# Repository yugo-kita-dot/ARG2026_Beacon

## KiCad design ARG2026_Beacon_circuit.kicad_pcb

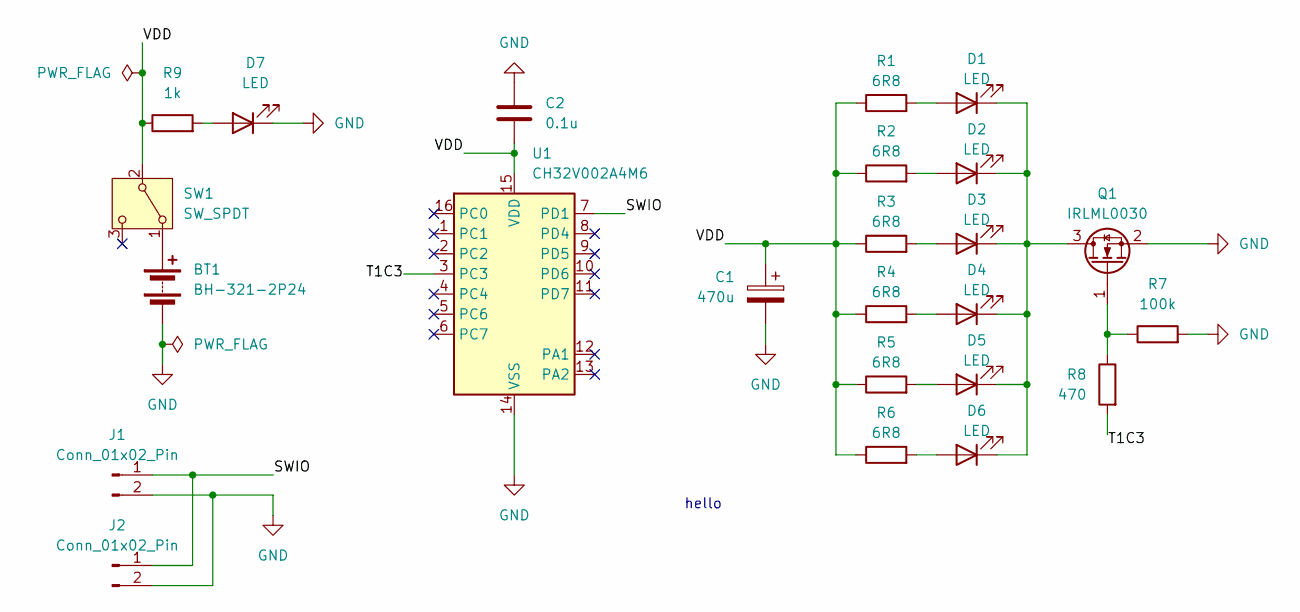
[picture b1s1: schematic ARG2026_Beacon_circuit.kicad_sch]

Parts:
BT1: BH-321-2P24
C1: 470u; CP_Radial_D8.0mm_P3.50mm
C2: 0.1u; C_Rect_L4.0mm_W2.5mm_P2.50mm
D1, D2, D3, D4, D5, D6: LED; LED_Rectangular_W5.0mm_H2.0mm
D7: LED; LED_D3.0mm
J1, J2: Conn_01x02_Pin; PinHeader_1x02_P2.54mm_Vertical
Q1: IRLML0030; SOT-23
R1, R2, R3, R4, R5, R6: 6R8; R_Axial_DIN0207_L6.3mm_D2.5mm_P10.16mm_Horizontal
R7: 100k; R_Axial_DIN0207_L6.3mm_D2.5mm_P10.16mm_Horizontal
R8: 470; R_Axial_DIN0207_L6.3mm_D2.5mm_P10.16mm_Horizontal
R9: 1k; R_Axial_DIN0207_L6.3mm_D2.5mm_P10.16mm_Horizontal
SW1: SW_SPDT; SW_Slide-03_Wuerth-WS-SLTV_10x2.5x6.4_P2.54mm
U1: CH32V002A4M6; STC_SOP-16_3.9x9.9mm_P1.27mm

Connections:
/SWIO: J1.1, J2.1, U1.7 (PD1)
/T1C3: R8.2, U1.3 (PC3)
/VDD: C1.1, C2.2, R1.1, R2.1, R3.1, R4.1, R5.1, R6.1, R9.1, SW1.2 (B), U1.15 (VDD)
GND: BT1.2 (-), C1.2, C2.1, D7.1 (K), J1.2, J2.2, Q1.2 (S), R7.2, U1.14 (VSS)
unnamed: BT1.1 (+), SW1.1 (A)
unnamed: D1.2 (A), R1.2
unnamed: D1.1 (K), D2.1 (K), D3.1 (K), D4.1 (K), D5.1 (K), D6.1 (K), Q1.3 (D)
unnamed: D2.2 (A), R2.2
unnamed: D3.2 (A), R3.2
unnamed: D4.2 (A), R4.2
unnamed: D5.2 (A), R5.2
unnamed: D6.2 (A), R6.2
unnamed: D7.2 (A), R9.2
unnamed: Q1.1 (G), R7.1, R8.1

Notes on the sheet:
hello

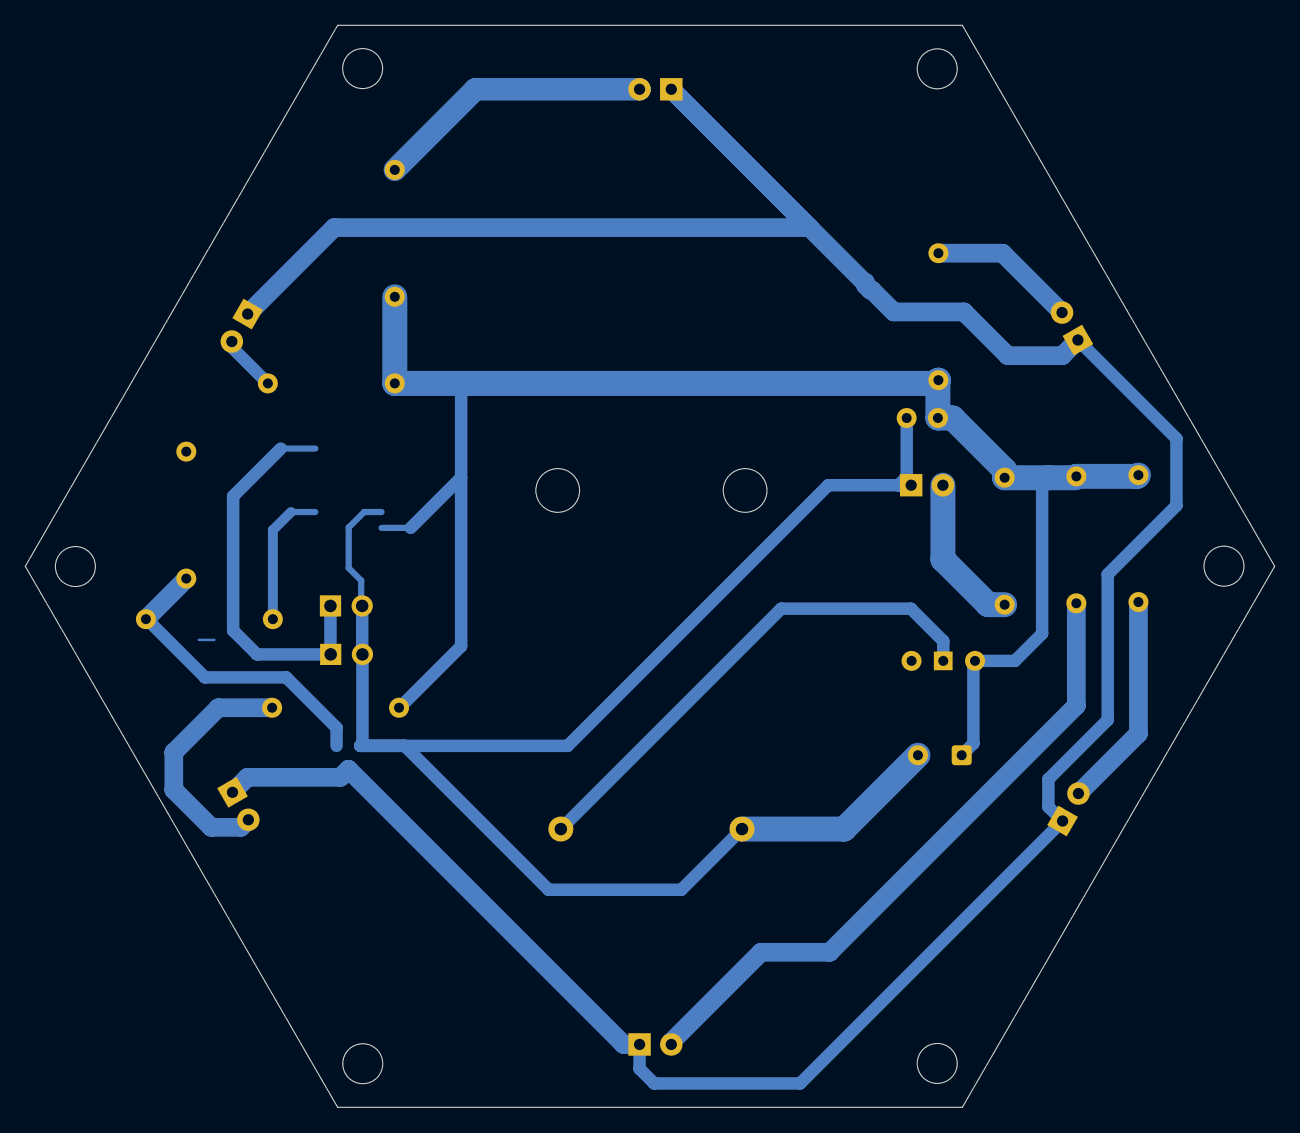
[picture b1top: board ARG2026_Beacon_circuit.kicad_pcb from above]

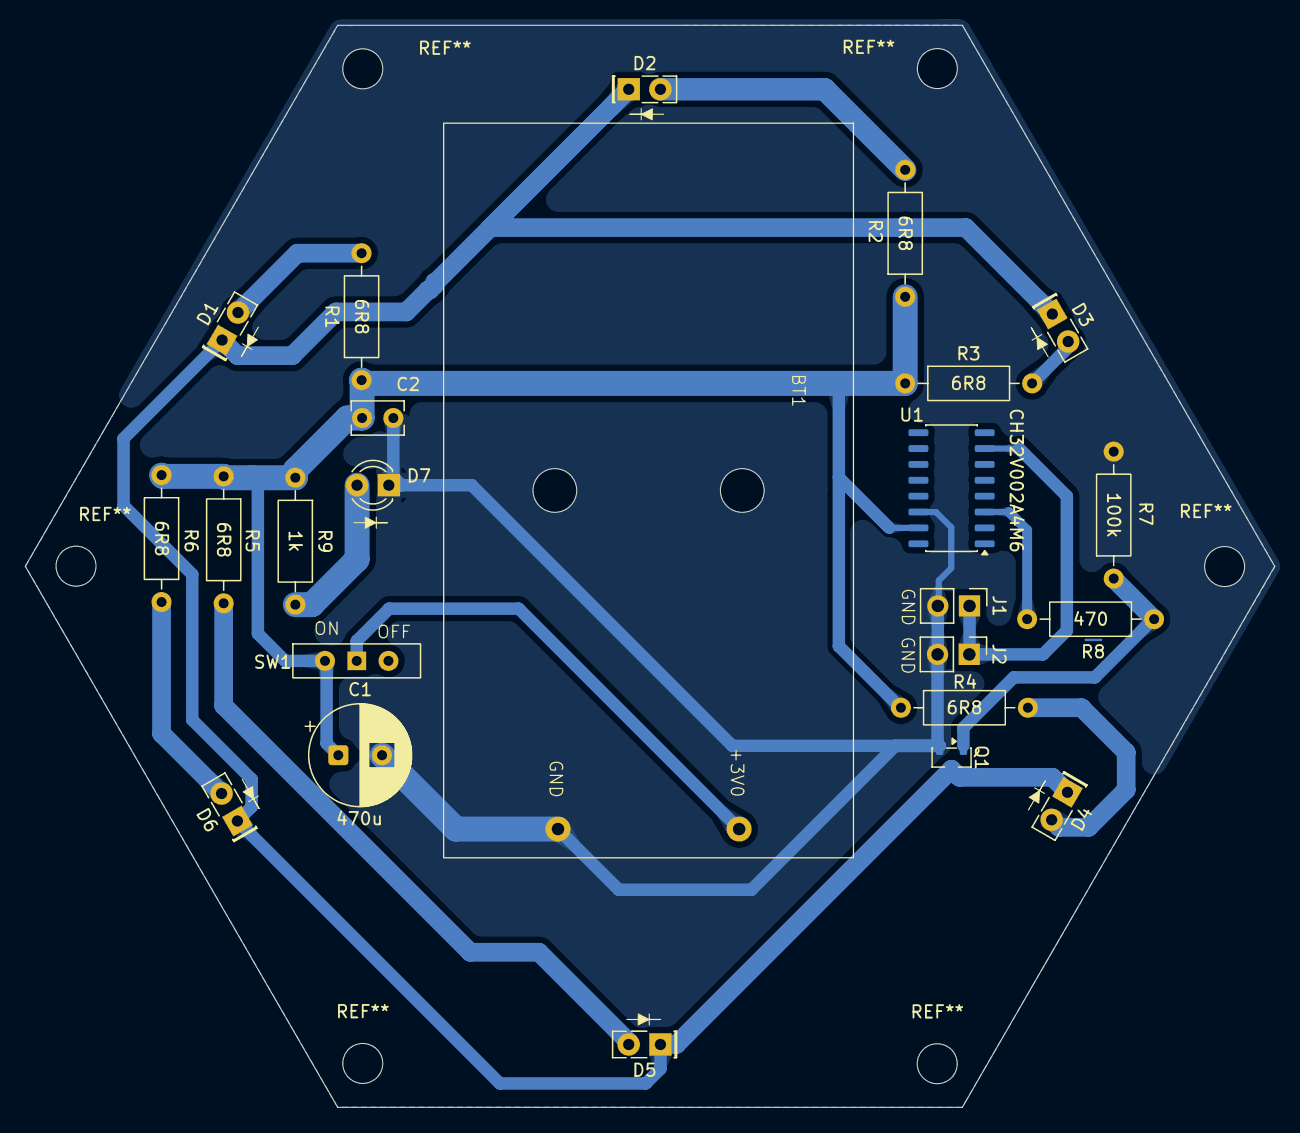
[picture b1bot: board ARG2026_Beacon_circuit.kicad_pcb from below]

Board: 2 copper layers, 100.0 x 86.6 mm, 24 parts (24 on the bottom side), 14 nets.
